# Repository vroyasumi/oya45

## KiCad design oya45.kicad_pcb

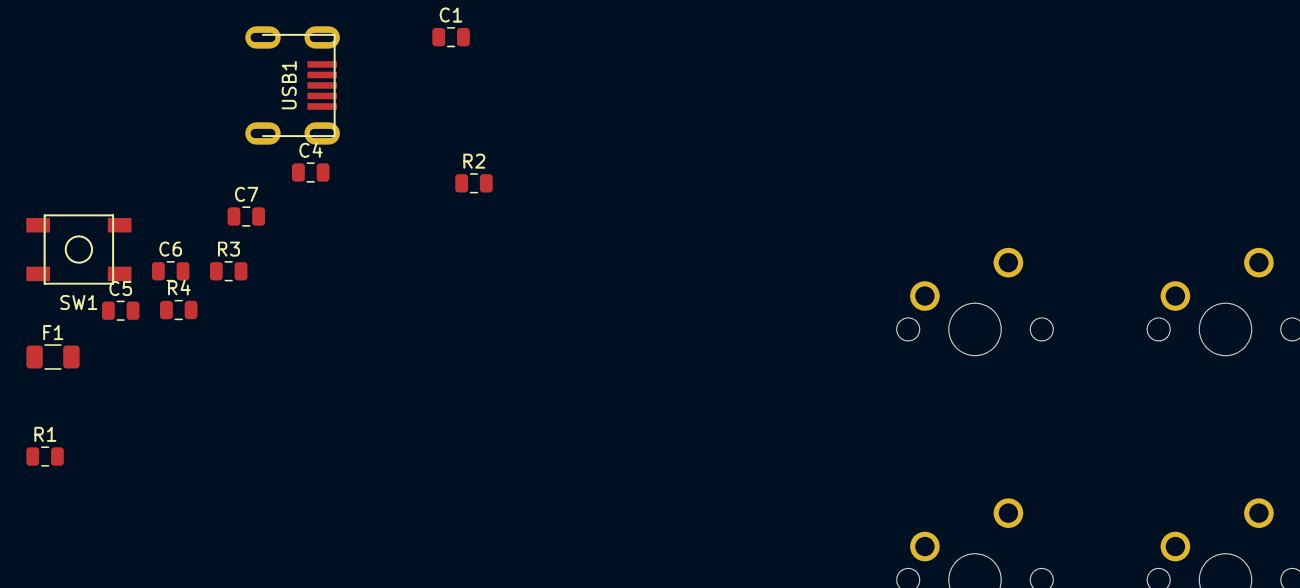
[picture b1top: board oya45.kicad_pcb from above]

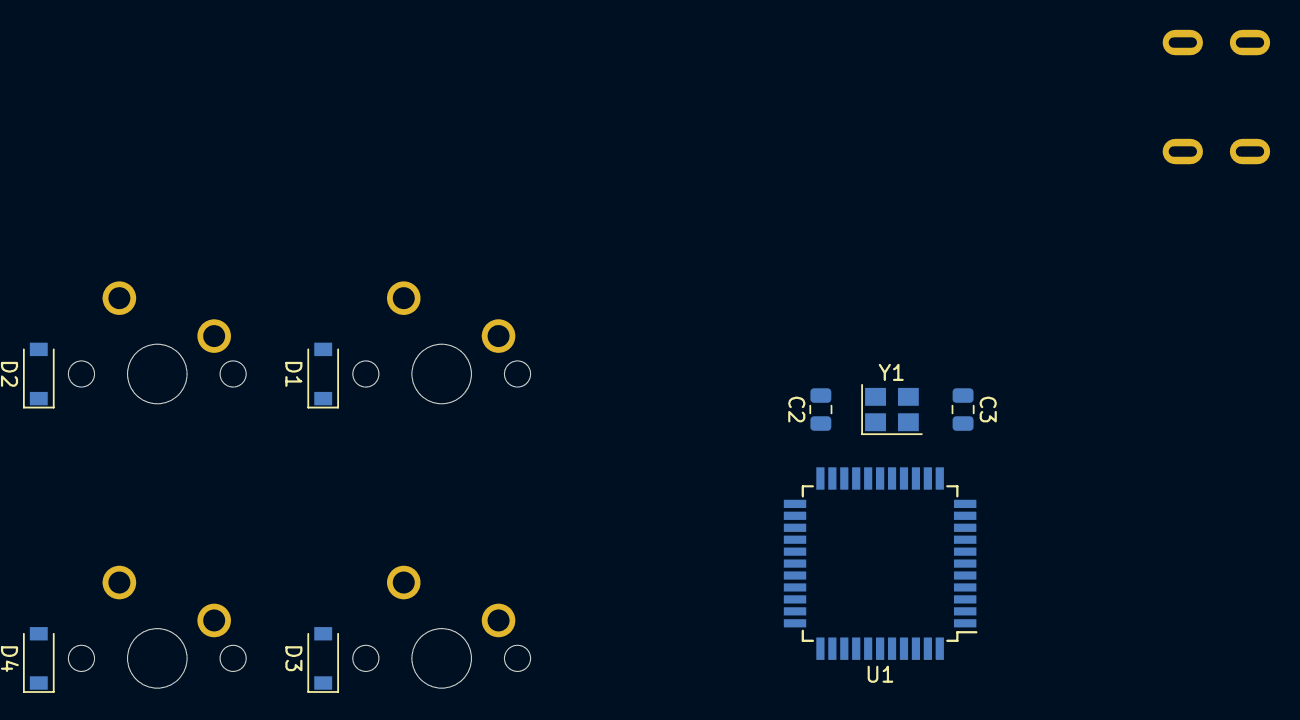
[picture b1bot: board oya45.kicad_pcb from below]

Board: 2 copper layers, 24 parts (8 on the bottom side), 20 nets, no tracks yet.

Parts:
C1, C4, C5, C7: 0.1uF; C_0805_2012Metric
C2, C3: 22pF; C_0805_2012Metric
C6: 1uF; C_0805_2012Metric
D1, D2, D3, D4: SOD_123; D_SOD-123
F1: 500mA; Fuse_1206_3216Metric
MX1, MX2, MX3, MX4: MX-NoLED; MXOnly-1U-NoLED
R1, R2: 22; R_0805_2012Metric
R3, R4: 10k; R_0805_2012Metric
SW1: SW_Push; SKQG-1155865
U1: ATmega32U4-AU; TQFP-44_10x10mm_P0.8mm
USB1: Molex-0548190589
Y1: Crystal_GND24_Small; Crystal_SMD_3225-4Pin_3.2x2.5mm

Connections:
+5V: C1.1, C4.1, C5.1, C7.1, F1.1, R3.1, U1.2, U1.7, U1.14, U1.24, U1.34, U1.44
COL0: MX1.1, MX2.1
COL1: MX3.1, MX4.1
D+: R2.2, USB1.3
D-: R1.2, USB1.4
GND: C1.2, C2.2, C3.2, C4.2, C5.2, C6.2, C7.2, R4.1, SW1.1, U1.5, U1.15, U1.23, U1.35, U1.43, USB1.1, Y1.2, Y1.4
unnamed: C2.1, U1.17, Y1.1
unnamed: C3.1, U1.16, Y1.3
unnamed: C6.1, U1.6
unnamed: D1.2, MX1.2
unnamed: D2.2, MX2.2
unnamed: D3.2, MX3.2
unnamed: D4.2, MX4.2
unnamed: R1.1, U1.3
unnamed: R2.1, U1.4
unnamed: R3.2, SW1.2, U1.13
unnamed: R4.2, U1.33
ROW0: D1.1, D3.1
ROW1: D2.1, D4.1
VCC: F1.2, USB1.5

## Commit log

2021-08-27 beginning
2021-08-27 Add submodules
2021-08-27 Add footprint libraries
2021-08-28 schematics
2021-08-28 schematics finish
2021-08-28 schematicfinish1
2021-08-28 test finish
2021-08-28 Added keebio libraries
